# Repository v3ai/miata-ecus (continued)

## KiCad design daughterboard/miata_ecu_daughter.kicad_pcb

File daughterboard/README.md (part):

# Miata ECU — daughterboard rev 0.10 (routed, unverified)

125 × 76 mm, **6 layers**. All SMD parts are on top; the two 1×40 2.54 mm male headers are mounted on the
**bottom side** (plastic under the board, pins pointing down) so the board plugs straight into female
headers on the year-specific motherboard. J1 on the top edge carries power and outputs, J2 on the
bottom edge carries inputs, comms and the LSU 4.9 wideband sensor.

## What changed in rev 0.10
Same outline, same J1/J2 pinout except J2-24 / J2-25; **six layers** instead of four. A rev 0.10 daughterboard goes
with motherboard rev 0.13 (1989-95) or 0.9 (1996-2005); it also fits the earlier motherboards, without the new
inputs. Background and numbers: `VERIFICATION.md`, [Rev 0.10](../VERIFICATION.md#rev-010-six-layers-injector-clamps-card-socket-two-more-inputs-2026-11-13),
and the audit in `research/rev0.10_design_audit.md`.
- **Injector clamp per injector** (D42-D45 ES1D, D46-D49 TPSMC16A): a fast diode from each injector driver's drain to
  a 16 V TVS that returns to the battery input. The turn-off energy goes there instead of through the driver's own
  clamp: 8.8 mJ per shot instead of 15.3 mJ with 20 mH injectors, peak 32 V instead of 43 V. The injector current
  takes about 0.16 ms longer to fall, so **check the injector dead time in the tune**.
- **220 Ω in series with each low-side driver input** (R152-R159): ST's VND7NV04 rating asks for at least 150 Ω.
- **microSD socket** J4 (Molex 47219-2001, hinged lid) on SPI2 with 47 kΩ pull-ups on every line but the clock.
  Rated -20 to +85 °C.
- **Two more inputs on J2-24 and J2-25** (a spare UART up to rev 0.9): flex-fuel sensor frequency (PC6, 10 µs filter)
  and nitrous arm (PC7, 100 µs filter), each through 10 kΩ and clamped to 3.3 V. The motherboard adds the sensor's
  pull-up and the switch's pull-down.
- **Check-engine lamp** driven from its processor pin directly (R160), outside the shared driver enable, so the
  firmware can light it on a fatal error.
- **Battery voltage** sensed at the battery input itself (was after the reverse diode and fuse, 0.3-0.4 V low).
- **Logic supply:** fuse F1 1.1 A hold (was 0.5 A), inductor L1 2.2 µH 7 A moulded, 100 nF (C71) at the buck
  converter's input pins.
- **Six layers:** F.Cu, ground plane, two inner signal layers, +3V3 plane, B.Cu. Every rev 0.9 part keeps its place
  except U14, F1, L1, the LED column (1.5 mm lower), the debug pads J3 and the two input clamps D36/D37 with their
  resistors. Inner copper is 15 µm against 35 µm outside, so the injector, valve, logic-supply and USB-supply nets
  stay on the outer layers; `scripts/track_current.py` checks every current-carrying track against its layer.
- **Heat:** each clamp TVS stands under its driver on its own copper column on all four signal layers (about
  176-196 mm² effective). A model of the whole board (`firmware/tools/board_thermal.py`) puts the board 23-31 °C
  above the air around it at sustained 7200 rpm with 20 mH injectors, the injector drivers 30-41 °C, the clamp TVSs
  43-52 °C and the processor 32-40 °C (sequential; 1989-93 cars run warmer, see `VERIFICATION.md`).
- **Routed from scratch** (`scripts/daughter_make.sh`): `route.py` in six-layer mode, then the new exact-geometry
  finisher `scripts/finish_route.py` for the connections and plane vias the grid router left. DRC: 0 unconnected,
  0 clearance errors.

## What changed in rev 0.9
Layout only; the circuit is rev 0.8's.
- **J1 back on the top edge, J2 on the bottom edge**, as up to rev 0.7, with the four mounting holes in the corners.
  The 16 mm strip of output drivers that rev 0.8 put above J1 now sits just below it: each VND7NV04 (Q1-Q8) stands
  with its tab up against its own J1 pin and its leads facing the level shifters, and the relay switches, the
  ignition diodes and pull-down switches and their resistors are mirrored the same way. Everything else keeps its
  rev 0.8 place and copper.
- **Drain copper** per driver: 84-100 mm² on F.Cu and 95-108 mm² on each of In2.Cu and B.Cu (the column now runs from the board edge down past the driver's leads), joined by 34-42 thermal vias (most in the tab pad; order them filled and
  capped). Estimated junction to ambient 48 °C/W, as in rev 0.8 (sequential injectors at 90 % duty, 7200 rpm, 85 °C ambient: 109 °C).
- **On the motherboards** the daughterboard sits 16 mm lower, centred top to bottom (42 mm from the top edge, as up to
  rev 0.7): JD1 and the upper standoffs are at their rev 0.7 places, JD2, the lower standoffs and the AUX header 16 mm
  lower. A rev 0.9 daughterboard needs a motherboard of rev 0.9 or later (1989-95; 1989-93 is now rev 0.11) or 0.7 (1996-2005).
- **Re-routed incrementally:** the rev 0.8 copper was kept everywhere except the nets of the moved parts
  (`route_eco.py`), which `route.py` routed again; four connections were finished by hand (`hand_route_all.py`).
  DRC: 0 unconnected, 0 clearance errors.

## What changed in rev 0.8
Fixes for what the rev 0.7 checks still flagged (`VERIFICATION.md`, [Rev 0.8](../VERIFICATION.md#rev-08-driver-temperature-and-protected-outputs)):
driver temperature, unprotected relay and ignition outputs, the sensor 5 V, the LSU drive wires, the CAN transceivers
and the AUX UART. Existing designators are unchanged where the part stays; new parts have new numbers.
- **Board 16 mm taller (125 × 76 mm).** The new strip along the top edge, above J1, sits over free motherboard space
  on every year (nothing on any motherboard is under it). J1, J2 and the four holes keep their places relative to each
  other, so the motherboards' sockets and standoffs don't move.
- **Low-side drivers Q1-Q8: ST VND7NV04** (DPAK, C155605) instead of the NCV8406A (SOT-223): 60 mΩ instead of 90-210,
  a 200 mJ clamp rating and 2.1 °C/W junction to case. They stand in the new strip, each with its tab down onto its
  own J1 pin, on a column of drain copper on F.Cu, In2.Cu and B.Cu (about 300 mm² per driver over the three layers)
  joined by 28-34 thermal vias, most of them inside the tab pad (`scripts/tab_copper.py`). Estimated junction to
  ambient 48 °C/W (rev 0.7: 109). Sequential injectors at 90 % duty, 7200 rpm, worst-case Rds(on): 84 °C at 60 °C
  ambient, 110 °C at 85 °C (rev 0.7: thermal shutdown). This is the "heat sink": copper and vias, no bolt-on part,
  since the board sits flat in the stock case. **Order the board with the vias epoxy-filled and capped** (JLC's
  via-in-pad process) so solder doesn't wick away from the tabs.
- **Relay, lamp and tach outputs: seven ZXMS6004FF protected low sides** (Q9-Q15, Diodes IntelliFET: current limit,
  thermal shutdown, 60 V clamp) instead of the ULN2003, driven at 5 V by a second SN74LVC4245A (U12) on the same
  enable as the other drivers, with 10k pull-downs (RN2, RN3). A relay or lamp wire shorted to battery now limits
  instead of burning a ULN channel.
- **Ignition outputs protected:** each TC4427 channel sources through its 100 Ω (now 1206) and a B5819W Schottky
  (D31-D34), and a ZXMS6004FF (Q16-Q19, gates from a 74HCT04, U13) pulls the output low. A coil wire shorted to battery
  just reverse-biases the Schottky. R144-R147 (3.3k, 1206) give the spark edge a defined fall with the pull-down off;
  3.3k keeps them inside their rating with a coil wire held at 24 V.
- **Protected harness 5 V:** a second TLS115 (U14) tracking +5V, out on J1 pin 13 (was a ground pin) to the harness's
  sensor 5 V cavities and the AUX header. The first TLS115 now feeds only the MAP sensor on the motherboard, so a
  sensor 5 V wire shorted to battery no longer takes the MAP reading or back-feeds the board. CLT/IAT bias from it;
  the hall pull-ups from it through a common-anode Schottky pair (D35), so a crank or cam wire shorted to battery
  puts nothing into its pull-up.
- **+3V3 shunt clamp:** a TL431 (U15) at 3.56 V drives a BCP53 PNP (Q20) that sinks fault current pushed into +3V3
  through the input clamps, with 2 × 100 µF bulk (C63, C68). Simulated with 1 A pushed in: 3.93 V peak for the first
  microseconds, then 3.56 V (the MCUs' absolute maximum is 4.0 V).
- **LSU drive wires:** F2 (0.1 A PTC) in the VM wire, Schottky clamps from the pump (D40) and virtual-ground (D41)
  drive nodes to +3V3, R108-R110 in 1206 and R137 22k. A short of IP, RT or VM to battery no longer reaches U101's
  outputs or the F103; the 1206 resistors take the short while it lasts (check or replace them after one).
  Firmware: VM_RESISTOR_VALUE 11.6 Ω (R109 + F2).
- **CAN: TI TCAN1042V-Q1** (U10, U106) instead of the SN65HVD230: ±58 V bus fault protection and −40 to 125 °C.
  Supplied from +5V (C67, C122), with 3.3 V I/O.
- **AUX UART:** 10k series resistors (R139, R140) and BAT54S clamps (D36, D37) on PC6/PC7.
- **Battery and ignition sense:** BAT54WS clamps D38/D39 on the dividers' ADC nodes.
- **Switch inputs: 22k/10k dividers** (was 33k): a 12 V signal at 9 V cranking now gives 2.81 V at the MCU, above ST's
  tested 2.31 V threshold. The hall series resistors R61/R63 are 0603.
- **Status LEDs:** comms and warning moved from PD13/PD14 to PC8/PC9 (PD12 run and PD15 error unchanged); the four
  adjacent PD pins left no way out for the fourth LED line. The board firmware is updated to match.
- **Re-routed incrementally** from the rev 0.7 copper (the old layout moved down 16 mm, `scripts/route_eco.py`), then
  `route.py`'s finish passes. The last connections around the wideband MCU and the LED lines were routed by hand
  (`scripts/hand_route.py`, chained by `hand_route_all.py`; a few short nets ripped up and rerouted in a better order),
  and `scripts/clean_dangling.py` removed the stubs that left. DRC: 0 unconnected, 0 clearance errors.

## What changed in rev 0.7
Fixes for the findings of the 2026-11-02 expanded circuit simulation and fault checks (`VERIFICATION.md`, findings
N1-N9). Existing designators are unchanged; new parts have new numbers.
- **U4 is an ST LDL1117S33R** (low dropout, same SOT-223 pinout) instead of the AMS1117-3.3. With about 1 V of dropout,
  the AMS1117 let the wideband MCU's VDDA (REF3033) run up to 0.95 V above its VDD while +5V rose or fell (power-up,
  key-off, crank dips; ST allows 0.3 V). The new part also keeps +3V3 up through an ISO 16750-2 level II crank, and
  is rated from -40 C.
- **D30 (BAT54WS) from the wideband MCU's VDDA to +3V3.** The low-dropout regulator alone still let VDDA lead VDD by
  about 0.8 V at key-off and in a slow brown-out, when the REF3033 holds up longer than +3V3; the Schottky caps the
  difference at about 0.25 V in every case simulated.
- **Clamps on the eight analog inputs:** D19-D26 (BAT54WS Schottky) from each AN_ node to +3V3, after the 5.6k. A
  sensor wire shorted to battery put 9.2 V on its MCU pin; now about 3.55 V, with 1.9 mA into +3V3 instead of the
  MCU. The 5.6k series and the CLT/IAT 2.7k bias resistors are now 0603. A Schottky leaks a little into the input
  when the sensor reads near 0 V, more when hot: estimated 5 mV at the sensor at 60 °C (up to about 46 mV with a
  worst-case part). Compare TPS and CLT readings with a meter on a hot day.
- **Clamps on the three 12 V switch inputs:** D27-D29 (1N4148WS) to +3V3, as on the hall inputs (a battery-fed switch
  closed during a load dump overdrove the pin). D27/D28 stand between the series resistors; D29 lies below the VR2
  parts.
- **Hall input resistors in 0603:** a crank/cam wire shorted to 14.4 V puts 88 mW into its 1k pull-up. The pull-ups
  now stand vertically beside their 4.7k series resistors to fit the larger size.
- **Knock input:** R138 (2.2k) ahead of the coupling cap C44, so a knock wire shorted to battery no longer couples a
  14 V step straight into the op-amp's input diodes.
- **Wideband sense inputs:** R137 (10k) feeds the Nernst buffer (U101 pin 10) from the LSU_UN wire, and F103 PA1 is no
  longer wired to LSU_VM (the firmware never sampled it). A UN or VM wire shorted to battery no longer reaches those
  inputs directly. The pump and virtual-ground drive paths can't take series resistance, so a short of IP, RT or VM
  to battery still damages U101 (inherited from the FOME module).
- **Injector driver copper:** OUT_INJ1-4 copper zones on both outer layers around Q1-Q4's tabs (86-90 mm² each), with
  17-21 thermal vias each. Estimated junction-to-ambient 109 °C/W instead of 130. This helps but doesn't remove the
  limit: at sustained 90 % injector duty a driver still reaches thermal shutdown at 85 °C ambient (1989-93), and on
  the sequential years, where each driver also absorbs its injector's turn-off energy, already at 60 °C near 7200 rpm.
  See VERIFICATION.md, N8.
- **Re-routed incrementally:** only the nets around the changed parts were routed again; the rest of the rev 0.6
  copper is unchanged. DRC: 0 unconnected, 0 clearance.

## What changed in rev 0.6
- **Wideband MCU: STM32F103C8T6** (U102, LQFP-48) instead of the STM32F042K6T6, which has been scarce for years and
  was down to about 100 at JLCPCB/LCSC; the F103C8T6 has over 200k there. The module's analog front end is unchanged.
  - Pins: ESR drives and LEDs face left, heater PWM / battery sense / pump PWM / BOOT1 right, CAN and the
    programming UART up, analog inputs down (`scripts/wideband.py`, U2_PADS).
  - New parts: an 8 MHz crystal Y101 with 33 pF loads C119/C120 (the same crystal as the main MCU's; keeps CAN
    timing in spec over temperature), R135 holds BOOT1 low, C121 decouples the third VDD pin.
  - Programming link unchanged: PD8/PD9 to the F103's USART1 (PA10/PA9), PD10 to BOOT0, PD11 to NRST.
  - Firmware: rusEFI's wideband controller with this board's port (`firmware/wideband/miata_f1`), carried by the
    main firmware and written with "Flash on-board wideband". rusEFI's own over-CAN wideband update is for the F042
    module and does not apply.

## What changed in rev 0.5
The fixes from the verification review (`VERIFICATION.md` in the repository root). Existing designators are unchanged;
new parts have new numbers.
- **Parts JLCPCB stocks (rev 0.5b).** JLCPCB's BOM check found ten lines short of stock. The replacements fit the
  same footprints; details in `VERIFICATION.md`.
  - Q1-Q8: onsemi **NCV8406A** (SOT-223, same pinout, 60-70 V active clamp, current limit and thermal shutdown)
    instead of the AUIPS2041L.
  - F1: TECHFUSE nSMD050-33V (33 V rating). D11/D12: Littelfuse SMAJ33A. L1: FH CMI322513U2R2KT.
    Status LEDs: Hubei KENTO KT-0603 G/B/Y. C103: YAGEO 33 nF 50 V. R110: 62 Ω (was 61.9 Ω, inside its 1 % tolerance).
  - VR inputs (spares, no Miata year uses a VR sensor): U9 is now a **LM2903** dual comparator (TI, onsemi, UMW and
    others make it) instead of the MAX9926, which is out of stock everywhere. Each input gets a BAT54S clamp to GND
    and +5V and 100k to a 1.65 V bias, and each output 1M of hysteresis (D15-D18, R73-R80, C60). The board was
    re-routed for these parts; `scripts/daughter_patch.py` adds the one track the autorouter left open (HALL1,
    through a via under the MCU) and nudges AN_AUX3 clear of the new clamps.
  - `fab/jlcpcb_cpl.csv` now uses the gerbers' own coordinates (no offset), with JLC's rotation corrections for
    SOT-223, TO-252, SOT-23, SOIC, TSSOP, LQFP and the resistor arrays, read off JLC's placement preview.
  - From the parts-availability review: D6 is now Littelfuse's SMCJ30A and D9 a Diodes B360A (both mainstream
    parts stocked at JLCPCB and US distributors; same footprints and ratings).
  - U105's footprint is named SOT-23-5 to match the AD8628ARTZ (identical pads), and SW1/SW2 share one BOM line.
- **5 V drive for the low-side drivers.** The rev 0.4 drivers (AUIPS2041) are specified at a 4-5.5 V input, and
  rev 0.4 drove them at 3.3 V.
  - U11 (SN74LVC4245A, DIR low: B → A) now drives Q1-Q8 from the MCU's control pins.
  - Its output enable is pulled up (R71), so the injectors, idle valve, VVT, boost and alternator stay off through
    reset, boot, the bootloader and DFU. The firmware enables them on **PA8** (open drain, active low) once every
    output is configured. This also covers PB3/PB4's power-up states (SWO trace, JTAG pull-up).
  - R19-R26 now pull the driver side low. The firmware parks unused control pins with the MCU's pull-downs
    (rusEFI's own idea of an unused pin is a pull-up, which would turn the driver on).
- **BOOT1 (PB2) pulled low** (R72), so ST's USB DFU bootloader starts reliably.
- **No relay back-feed.** The ULN2003's COM pin goes to an SMAJ33A TVS (D11, 36.7-40.6 V breakdown) instead of
  +12V. A battery-fed relay coil (the 2003-05 main relay) can no longer power the ECU through the clamp diodes with
  the key off. Relay kick-back clamps at 43 V at most (ULN2003 limit 50 V), and the TVS stays off through a 35 V load
  dump on the relay feeds.
- **Fused, clamped logic supply.** D7 (battery) and D8 (ignition wake) feed F1 (0.5 A PTC), then D12 (SMAJ33A) on +12V.
  - This keeps the buck under its 44 V maximum in load-dump and ISO pulse tests, and clamps the ignition path too.
    D12's breakdown sits above the 35 V load-dump clamp, so the input TVS D6 takes that energy and D12 only sees fast
    spikes.
  - An internal short trips F1 instead of waiting on the car's fuse.
  - C16 is now 10 µF / 50 V, D9 is a 60 V 3 A Schottky (Diodes B360A), and C59 adds buck output capacitance.
- **Crank/cam input clamps.** D13/D14 (1N4148WS) clamp PE7/PE8 to +3V3. These 5 V-tolerant pins have no clamp of
  their own, so a crank/cam wire shorted to battery would otherwise destroy them.
- **Buck inductor L2** is now a Sunlord MWSA0603S-100MT (7 × 6.6 mm, 5.5 A saturation), above the LMR14020's
  3.8 A maximum current limit. The old 5 × 5 mm part saturated at 3.5 A.
- **Crystal load caps** C13/C14 are 33 pF (were 22 pF) to match the 20 pF crystal.
- The Tag-Connect SWD pads J3 moved right of the MCU to make room for U11.

## What changed in rev 0.4
- **Both MCUs flash over the one USB-C port.** The main MCU now has a programming link to the wideband MCU (U102):
  | Main MCU (U1, STM32F407) | Wideband MCU (U102, STM32F042) | Job |
  |---|---|---|
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
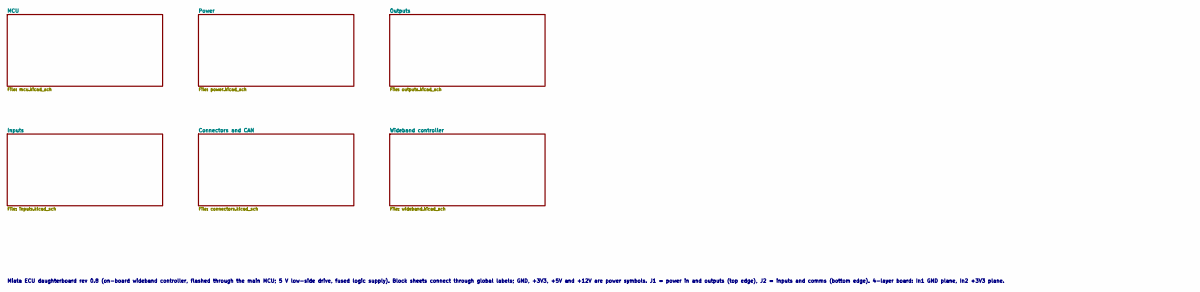
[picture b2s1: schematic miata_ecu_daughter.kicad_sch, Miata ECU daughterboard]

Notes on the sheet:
Miata ECU daughterboard rev 0.8 (on-board wideband controller, flashed through the main MCU; 5 V low-side drive, fused logic supply). Block sheets connect through global labels; GND, +3V3, +5V and +12V are power symbols. J1 = power in and outputs (top edge), J2 = inputs and comms (bottom edge). 4-l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

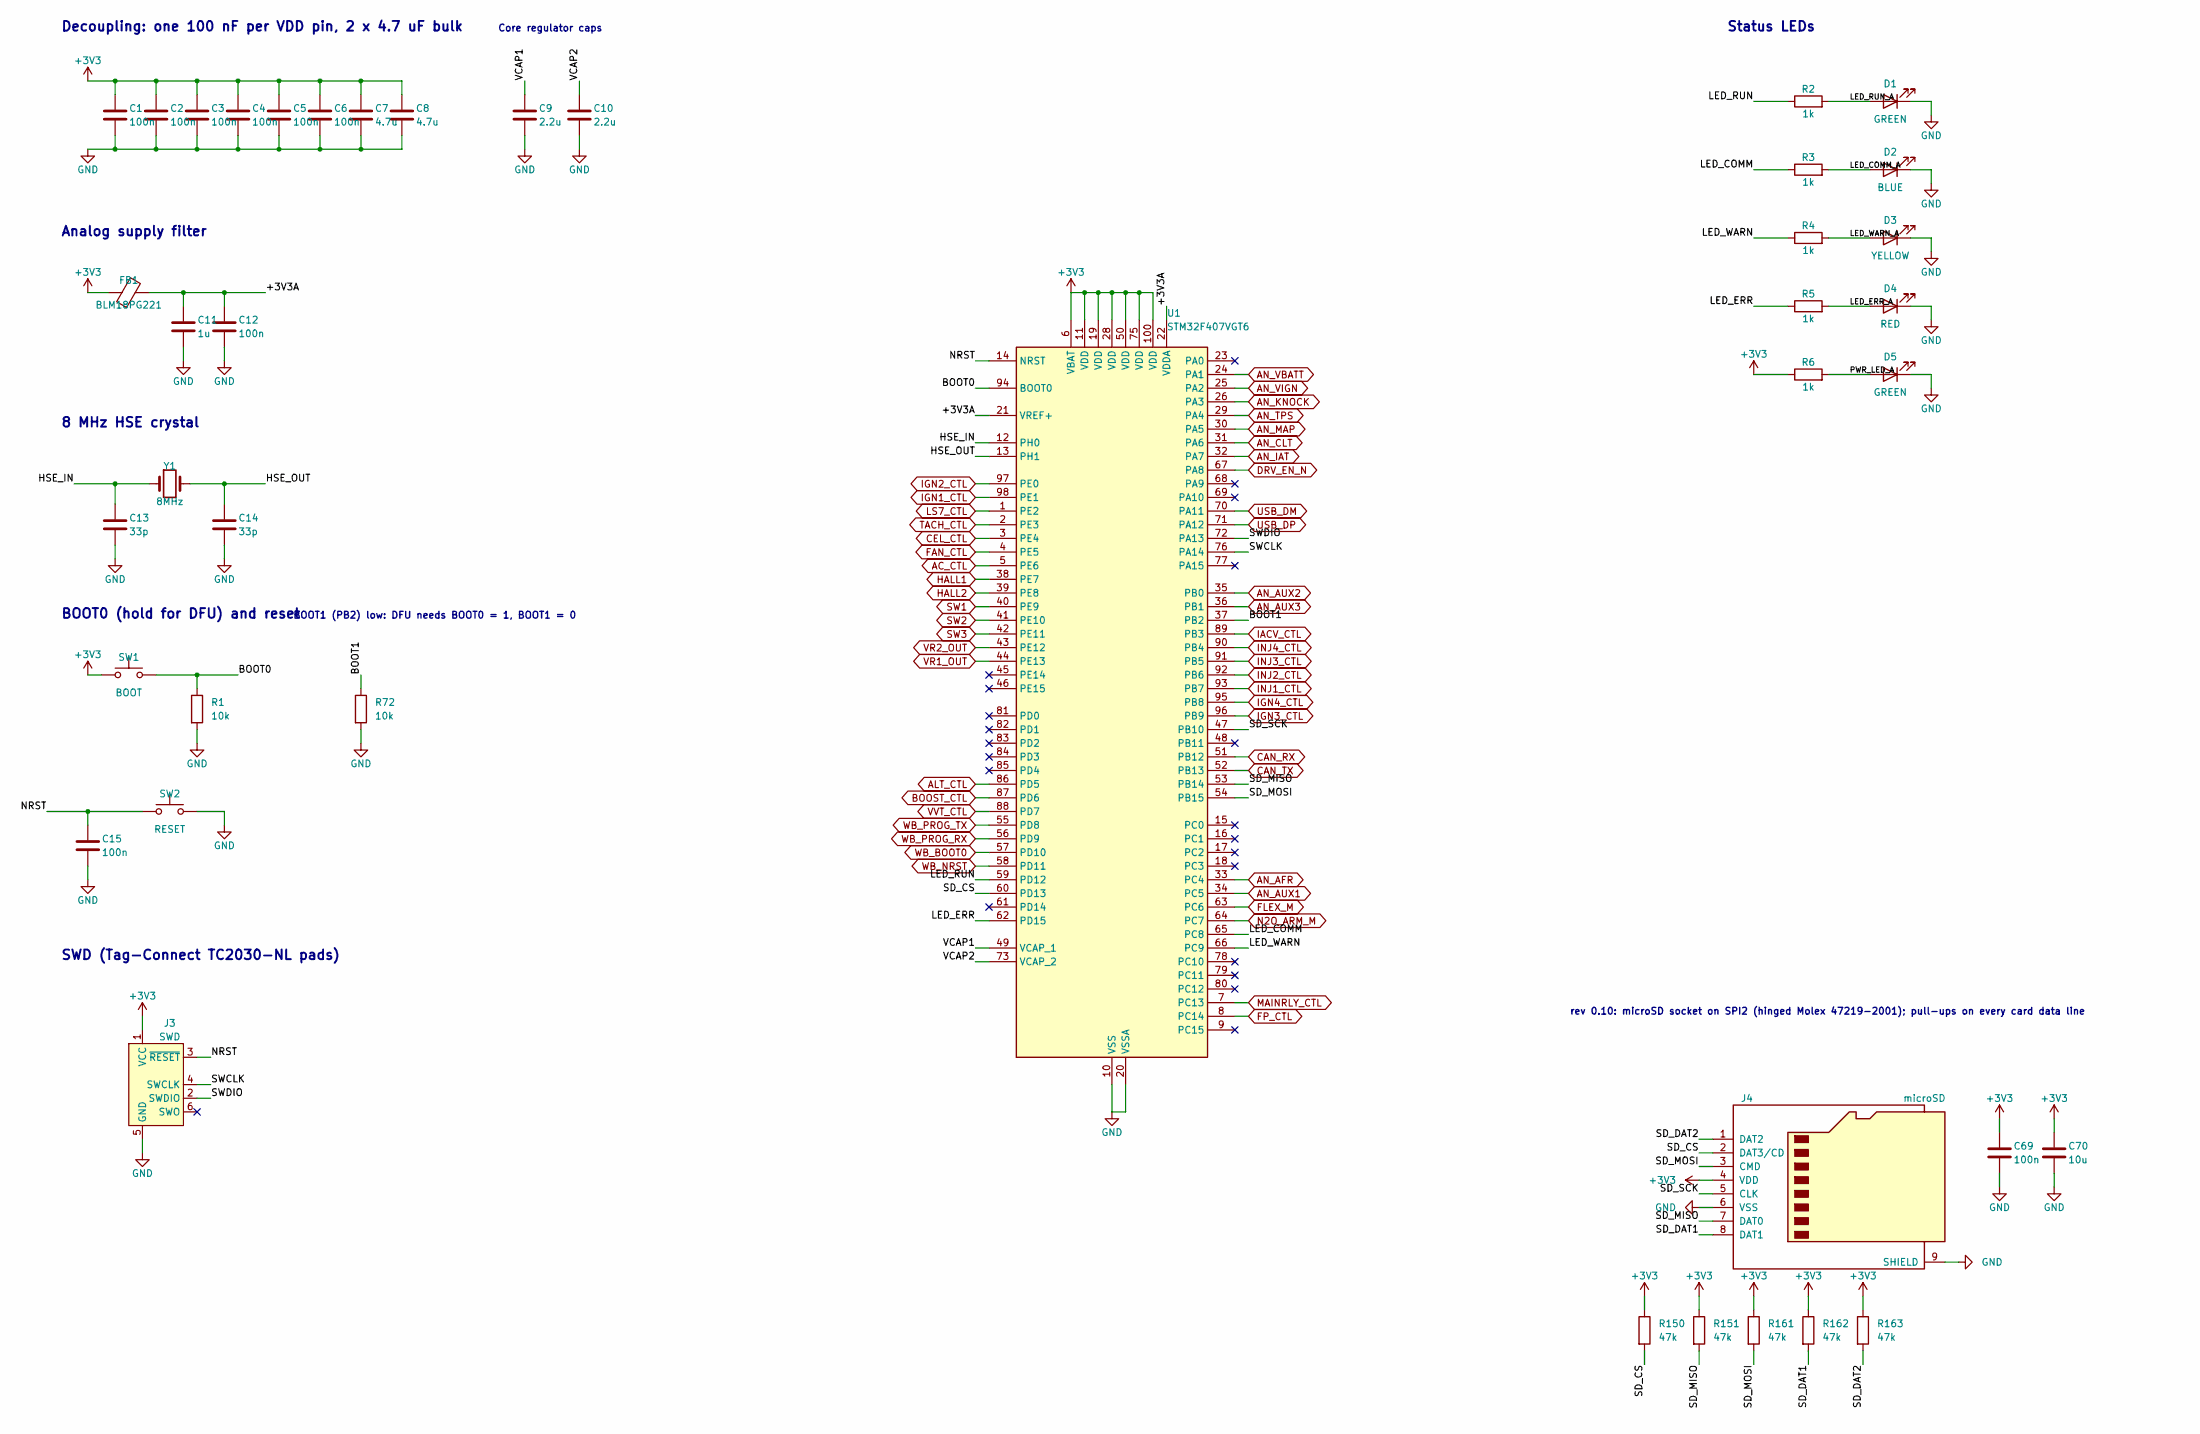
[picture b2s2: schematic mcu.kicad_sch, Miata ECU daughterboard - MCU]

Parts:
C1, C2, C3, C5, C6, C12, C15: 100n; C_0603_1608Metric; LCSC C14663
C4, C69: 100n; C_0402_1005Metric; LCSC C1525
C7, C8: 4.7u; C_0603_1608Metric; LCSC C19666
C9, C10: 2.2u; C_0603_1608Metric; LCSC C23630
C11: 1u; C_0603_1608Metric; LCSC C15849
C13, C14: 33p; C_0603_1608Metric; LCSC C1663
C70: 10u; C_0805_2012Metric; LCSC C15850
D1, D5: GREEN; LED_0603_1608Metric; LCSC C12624
D2: BLUE; LED_0603_1608Metric; LCSC C2288
D3: YELLOW; LED_0603_1608Metric; LCSC C2287
D4: RED; LED_0603_1608Metric; LCSC C2286
FB1: BLM18PG221; L_0603_1608Metric; LCSC C80165
J3: SWD; Tag-Connect_TC2030-IDC-NL_2x03_P1.27mm_Vertical
J4: microSD; microSD_HC_Molex_47219-2001; LCSC C164170
R1: 10k; R_0603_1608Metric; LCSC C25804
R2, R3, R4, R5, R6: 1k; R_0603_1608Metric; LCSC C21190
R72: 10k; R_0402_1005Metric; LCSC C25744
R150, R151, R161, R162, R163: 47k; R_0402_1005Metric; LCSC C25792
SW1: BOOT; SW_Push_1P1T_XKB_TS-1187A; LCSC C318884
SW2: RESET; SW_Push_1P1T_XKB_TS-1187A; LCSC C318884
U1: STM32F407VGT6; LQFP-100_14x14mm_P0.5mm; LCSC C12345
Y1: 8MHz; Crystal_SMD_5032-2Pin_5.0x3.2mm; LCSC C115962

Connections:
+3V3: C1.1, C2.1, C3.1, C4.1, C5.1, C6.1, C7.1, C8.1, C69.1, C70.1, FB1.1, J3.1 (VCC), J4.4 (VDD), R6.1, R150.1, R151.1, R161.1, R162.1, R163.1, SW1.1, U1.6 (VBAT), U1.11 (VDD), U1.19 (VDD), U1.28 (VDD), U1.50 (VDD), U1.75 (VDD), U1.100 (VDD); also elsewhere on the board
/MCU/+3V3A: C11.1, C12.1, FB1.2, U1.21 (VREF+), U1.22 (VDDA)
/MCU/BOOT0: R1.1, SW1.2, U1.94 (BOOT0)
/MCU/BOOT1: R72.1, U1.37 (PB2)
/MCU/HSE_IN: C13.1, U1.12 (PH0), Y1.1
/MCU/HSE_OUT: C14.1, U1.13 (PH1), Y1.2
/MCU/LED_COMM: R3.1, U1.65 (PC8)
/MCU/LED_COMM_A: D2.2 (A), R3.2
/MCU/LED_ERR: R5.1, U1.62 (PD15)
/MCU/LED_ERR_A: D4.2 (A), R5.2
/MCU/LED_RUN: R2.1, U1.59 (PD12)
/MCU/LED_RUN_A: D1.2 (A), R2.2
/MCU/LED_WARN: R4.1, U1.66 (PC9)
/MCU/LED_WARN_A: D3.2 (A), R4.2
/MCU/NRST: C15.1, J3.3 (~RESET), SW2.1, U1.14 (NRST)
/MCU/PWR_LED_A: D5.2 (A), R6.2
/MCU/SD_CS: J4.2 (DAT3/CD), R150.2, U1.60 (PD13)
/MCU/SD_DAT1: J4.8 (DAT1), R162.2
/MCU/SD_DAT2: J4.1 (DAT2), R163.2
/MCU/SD_MISO: J4.7 (DAT0), R151.2, U1.53 (PB14)
/MCU/SD_MOSI: J4.3 (CMD), R161.2, U1.54 (PB15)
/MCU/SD_SCK: J4.5 (CLK), U1.47 (PB10)
/MCU/SWCLK: J3.4 (SWCLK), U1.76 (PA14)
/MCU/SWDIO: J3.2 (SWDIO), U1.72 (PA13)
/MCU/VCAP1: C9.1, U1.49 (VCAP_1)
/MCU/VCAP2: C10.1, U1.73 (VCAP_2)
AC_CTL: U1.5 (PE6); also elsewhere on the board
ALT_CTL: U1.86 (PD5); also elsewhere on the board
AN_AFR: U1.33 (PC4); also elsewhere on the board
AN_AUX1: U1.34 (PC5); also elsewhere on the board
AN_AUX2: U1.35 (PB0); also elsewhere on the board
AN_AUX3: U1.36 (PB1); also elsewhere on the board
AN_CLT: U1.31 (PA6); also elsewhere on the board
AN_IAT: U1.32 (PA7); also elsewhere on the board
AN_KNOCK: U1.26 (PA3); also elsewhere on the board
AN_MAP: U1.30 (PA5); also elsewhere on the board
AN_TPS: U1.29 (PA4); also elsewhere on the board
AN_VBATT: U1.24 (PA1); also elsewhere on the board
AN_VIGN: U1.25 (PA2); also elsewhere on the board
BOOST_CTL: U1.87 (PD6); also elsewhere on the board
CAN_RX: U1.51 (PB12); also elsewhere on the board
CAN_TX: U1.52 (PB13); also elsewhere on the board
CEL_CTL: U1.3 (PE4); also elsewhere on the board
DRV_EN_N: U1.67 (PA8); also elsewhere on the board
FAN_CTL: U1.4 (PE5); also elsewhere on the board
FLEX_M: U1.63 (PC6); also elsewhere on the board
FP_CTL: U1.8 (PC14); also elsewhere on the board
GND: C1.2, C2.2, C3.2, C4.2, C5.2, C6.2, C7.2, C8.2, C9.2, C10.2, C11.2, C12.2, C13.2, C14.2, C15.2, C69.2, C70.2, D1.1 (K), D2.1 (K), D3.1 (K), D4.1 (K), D5.1 (K), J3.5 (GND), J4.6 (VSS), J4.9 (SHIELD), R1.2, R72.2, SW2.2, U1.10 (VSS), U1.20 (VSSA), U1.27 (VSS), U1.74 (VSS), U1.99 (VSS); also elsewhere on the board
HALL1: U1.38 (PE7); also elsewhere on the board
HALL2: U1.39 (PE8); also elsewhere on the board
IACV_CTL: U1.89 (PB3); also elsewhere on the board
IGN1_CTL: U1.98 (PE1); also elsewhere on the board
IGN2_CTL: U1.97 (PE0); also elsewhere on the board
IGN3_CTL: U1.96 (PB9); also elsewhere on the board
IGN4_CTL: U1.95 (PB8); also elsewhere on the board
INJ1_CTL: U1.93 (PB7); also elsewhere on the board
INJ2_CTL: U1.92 (PB6); also elsewhere on the board
INJ3_CTL: U1.91 (PB5); also elsewhere on the board
INJ4_CTL: U1.90 (PB4); also elsewhere on the board
LS7_CTL: U1.1 (PE2); also elsewhere on the board
MAINRLY_CTL: U1.7 (PC13); also elsewhere on the board
N2O_ARM_M: U1.64 (PC7); also elsewhere on the board
SW1: U1.40 (PE9); also elsewhere on the board
SW2: U1.41 (PE10); also elsewhere on the board
SW3: U1.42 (PE11); also elsewhere on the board
TACH_CTL: U1.2 (PE3); also elsewhere on the board
USB_DM: U1.70 (PA11); also elsewhere on the board
USB_DP: U1.71 (PA12); also elsewhere on the board
VR1_OUT: U1.44 (PE13); also elsewhere on the board
VR2_OUT: U1.43 (PE12); also elsewhere on the board
VVT_CTL: U1.88 (PD7); also elsewhere on the board
WB_BOOT0: U1.57 (PD10); also elsewhere on the board
WB_NRST: U1.58 (PD11); also elsewhere on the board
WB_PROG_RX: U1.56 (PD9); also elsewhere on the board
WB_PROG_TX: U1.55 (PD8); also elsewhere on the board

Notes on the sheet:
Decoupling: one 100 nF per VDD pin, 2 x 4.7 uF bulk
Core regulator caps
Analog supply filter
8 MHz HSE crystal
BOOT0 (hold for DFU) and reset
BOOT1 (PB2) low: DFU needs BOOT0 = 1, BOOT1 = 0
SWD (Tag-Connect TC2030-NL pads)
rev 0.10: microSD socket on SPI2 (hinged Molex 47219-2001); pull-ups on every card data line
Status LEDs

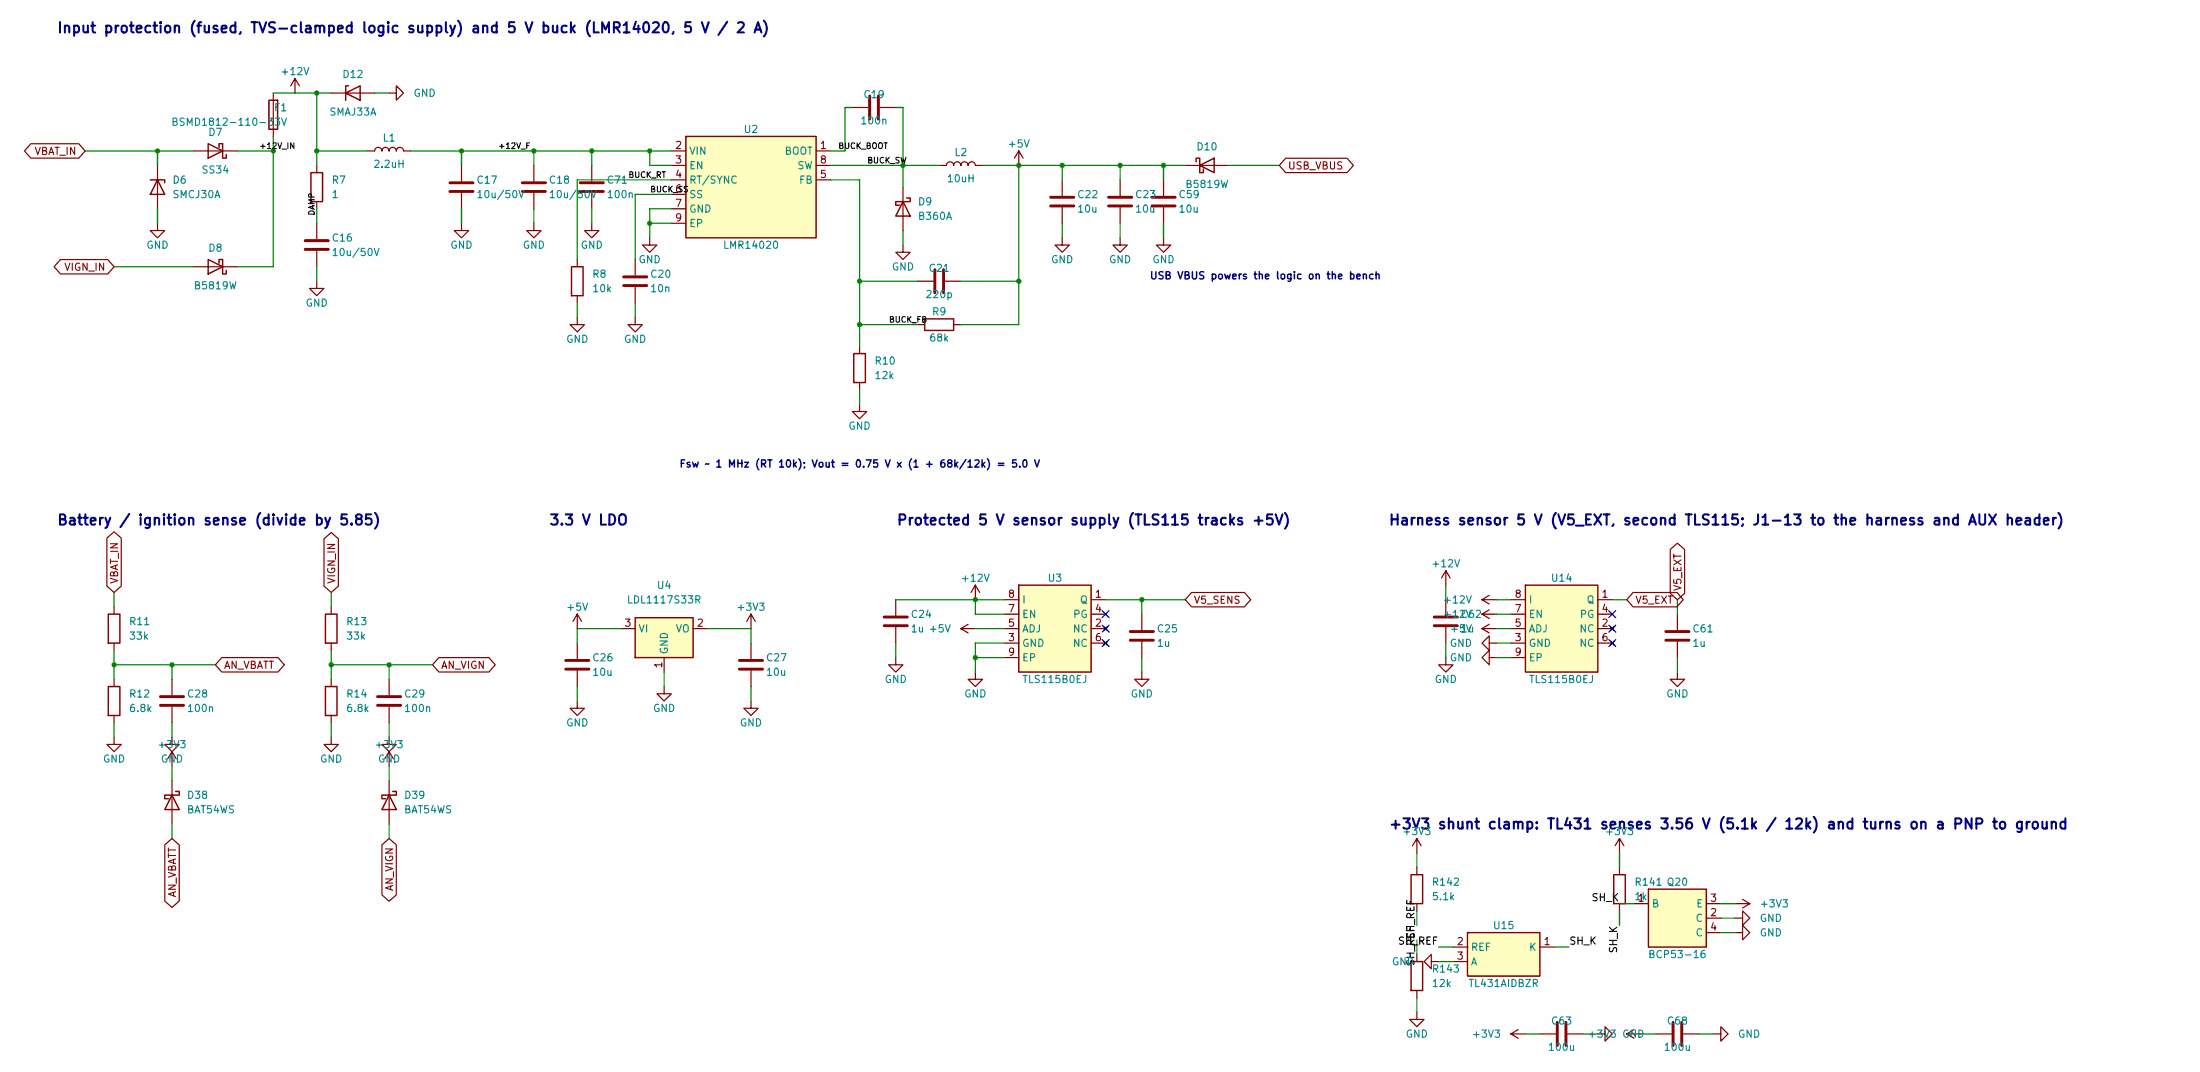
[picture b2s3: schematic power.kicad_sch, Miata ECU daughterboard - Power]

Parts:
C16, C17, C18: 10u/50V; C_1206_3216Metric; LCSC C13585
C19, C71: 100n; C_0603_1608Metric; LCSC C14663
C20: 10n; C_0603_1608Metric; LCSC C57112
C21: 220p; C_0603_1608Metric; LCSC C1603
C22, C23, C26, C27, C59: 10u; C_0805_2012Metric; LCSC C15850
C24, C25, C61, C62: 1u; C_0603_1608Metric; LCSC C15849
C28, C29: 100n; C_0402_1005Metric; LCSC C1525
C63, C68: 100u; C_1206_3216Metric; LCSC C15008
D6: SMCJ30A; D_SMC; LCSC C224048
D7: SS34; D_SMA; LCSC C8678
D8, D10: B5819W; D_SOD-123; LCSC C8598
D9: B360A; D_SMA; LCSC C94193
D12: SMAJ33A; D_SMA; LCSC C223988
D38, D39: BAT54WS; D_SOD-323; LCSC C124205
F1: BSMD1812-110-33V; Fuse_1812_4532Metric; LCSC C883150
L1: 2.2uH; L_Sunlord_MWSA0503S; LCSC C177247
L2: 10uH; L_Sunlord_MWSA0603S; LCSC C132141
Q20: BCP53-16; SOT-223; LCSC C85085
R7: 1; R_0603_1608Metric; LCSC C22936
R8: 10k; R_0603_1608Metric; LCSC C25804
R9: 68k; R_0603_1608Metric; LCSC C23231
R10, R143: 12k; R_0603_1608Metric; LCSC C22790
R11, R13: 33k; R_0402_1005Metric; LCSC C25779
R12, R14: 6.8k; R_0402_1005Metric; LCSC C25917
R141: 1k; R_0603_1608Metric; LCSC C21190
R142: 5.1k; R_0603_1608Metric; LCSC C23186
U2: LMR14020; SOIC-8-1EP_3.9x4.9mm_P1.27mm_EP2.29x3mm; LCSC C187824
U3, U14: TLS115B0EJ; Infineon_PG-DSO-8-27_3.9x4.9mm_EP2.65x3mm; LCSC C3743696
U4: LDL1117S33R; SOT-223-3_TabPin2; LCSC C435835
U15: TL431AIDBZR; SOT-23; LCSC C23892

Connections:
+3V3: C27.1, C63.1, C68.1, D38.1 (K), D39.1 (K), Q20.3 (E), R141.1, R142.1, U4.2 (VO); also elsewhere on the board
+5V: C21.1, C22.1, C23.1, C26.1, C59.1, D10.1 (K), L2.2, R9.1, U3.5 (ADJ), U4.3 (VI), U14.5 (ADJ); also elsewhere on the board
+12V: C24.1, C62.1, D12.1 (K), F1.2, L1.1, R7.1, U3.7 (EN), U3.8 (I), U14.7 (EN), U14.8 (I)
/Power/+12V_F: C17.1, C18.1, C71.1, L1.2, U2.2 (VIN), U2.3 (EN)
/Power/+12V_IN: D7.1 (K), D8.1 (K), F1.1
/Power/BUCK_BOOT: C19.1, U2.1 (BOOT)
/Power/BUCK_FB: C21.2, R9.2, R10.1, U2.5 (FB)
/Power/BUCK_RT: R8.1, U2.4 (RT/SYNC)
/Power/BUCK_SS: C20.1, U2.6 (SS)
/Power/BUCK_SW: C19.2, D9.1 (K), L2.1, U2.8 (SW)
/Power/DAMP: C16.1, R7.2
/Power/SH_K: Q20.1 (B), R141.2, U15.1 (K)
/Power/SH_REF: R142.2, R143.1, U15.2 (REF)
AN_VBATT: C28.1, D38.2 (A), R11.2, R12.1; also elsewhere on the board
AN_VIGN: C29.1, D39.2 (A), R13.2, R14.1; also elsewhere on the board
GND: C16.2, C17.2, C18.2, C20.2, C22.2, C23.2, C24.2, C25.2, C26.2, C27.2, C28.2, C29.2, C59.2, C61.2, C62.2, C63.2, C68.2, C71.2, D6.2 (A), D9.2 (A), D12.2 (A), Q20.2 (C), Q20.4 (C), R8.2, R10.2, R12.2, R14.2, R143.2, U2.7 (GND), U2.9 (EP), U3.3 (GND), U3.9 (EP), U4.1 (GND), U14.3 (GND), U14.9 (EP), U15.3 (A); also elsewhere on the board
USB_VBUS: D10.2 (A); also elsewhere on the board
V5_EXT: C61.1, U14.1 (Q); also elsewhere on the board
V5_SENS: C25.1, U3.1 (Q); also elsewhere on the board
VBAT_IN: D6.1 (K), D7.2 (A), R11.1; also elsewhere on the board
VIGN_IN: D8.2 (A), R13.1; also elsewhere on the board

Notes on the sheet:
Input protection (fused, TVS-clamped logic supply) and 5 V buck (LMR14020, 5 V / 2 A)
USB VBUS powers the logic on the bench
Fsw ~ 1 MHz (RT 10k); Vout = 0.75 V x (1 + 68k/12k) = 5.0 V
3.3 V LDO
Protected 5 V sensor supply (TLS115 tracks +5V)
Harness sensor 5 V (V5_EXT, second TLS115; J1-13 to the harness and AUX header)
+3V3 shunt clamp: TL431 senses 3.56 V (5.1k / 12k) and turns on a PNP to ground
Battery / ignition sense (divide by 5.85)

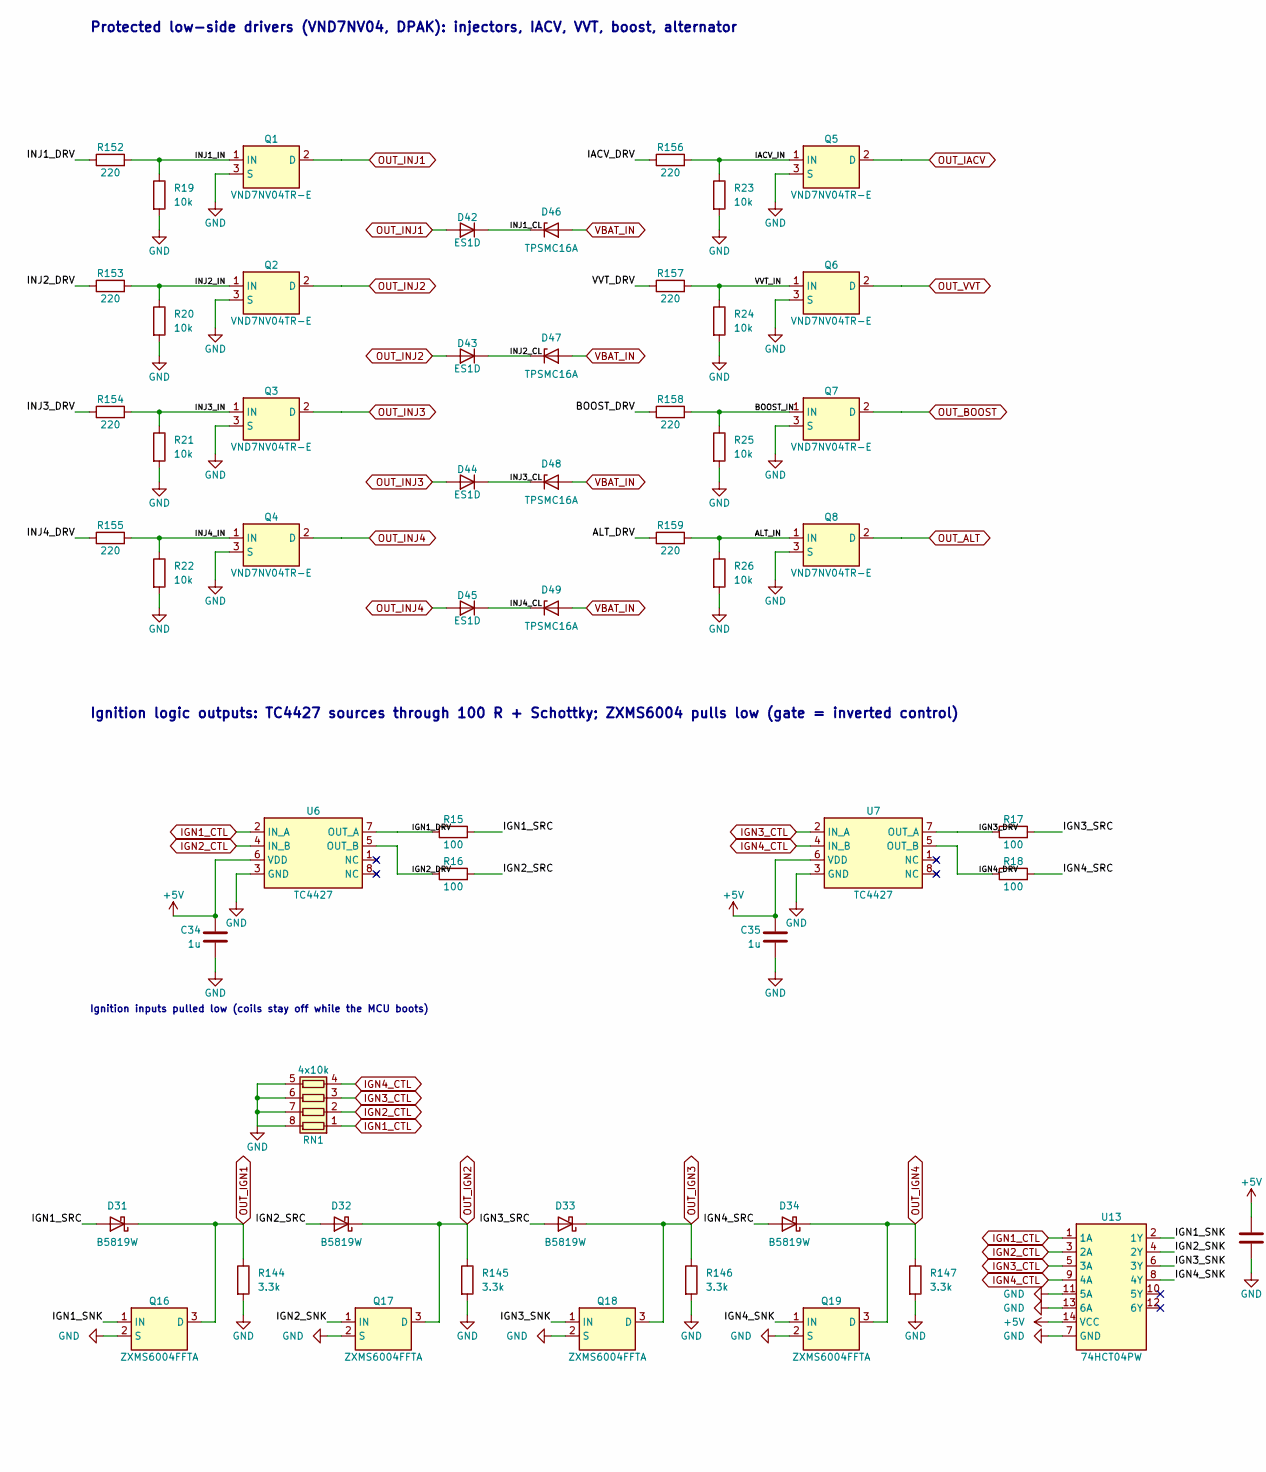
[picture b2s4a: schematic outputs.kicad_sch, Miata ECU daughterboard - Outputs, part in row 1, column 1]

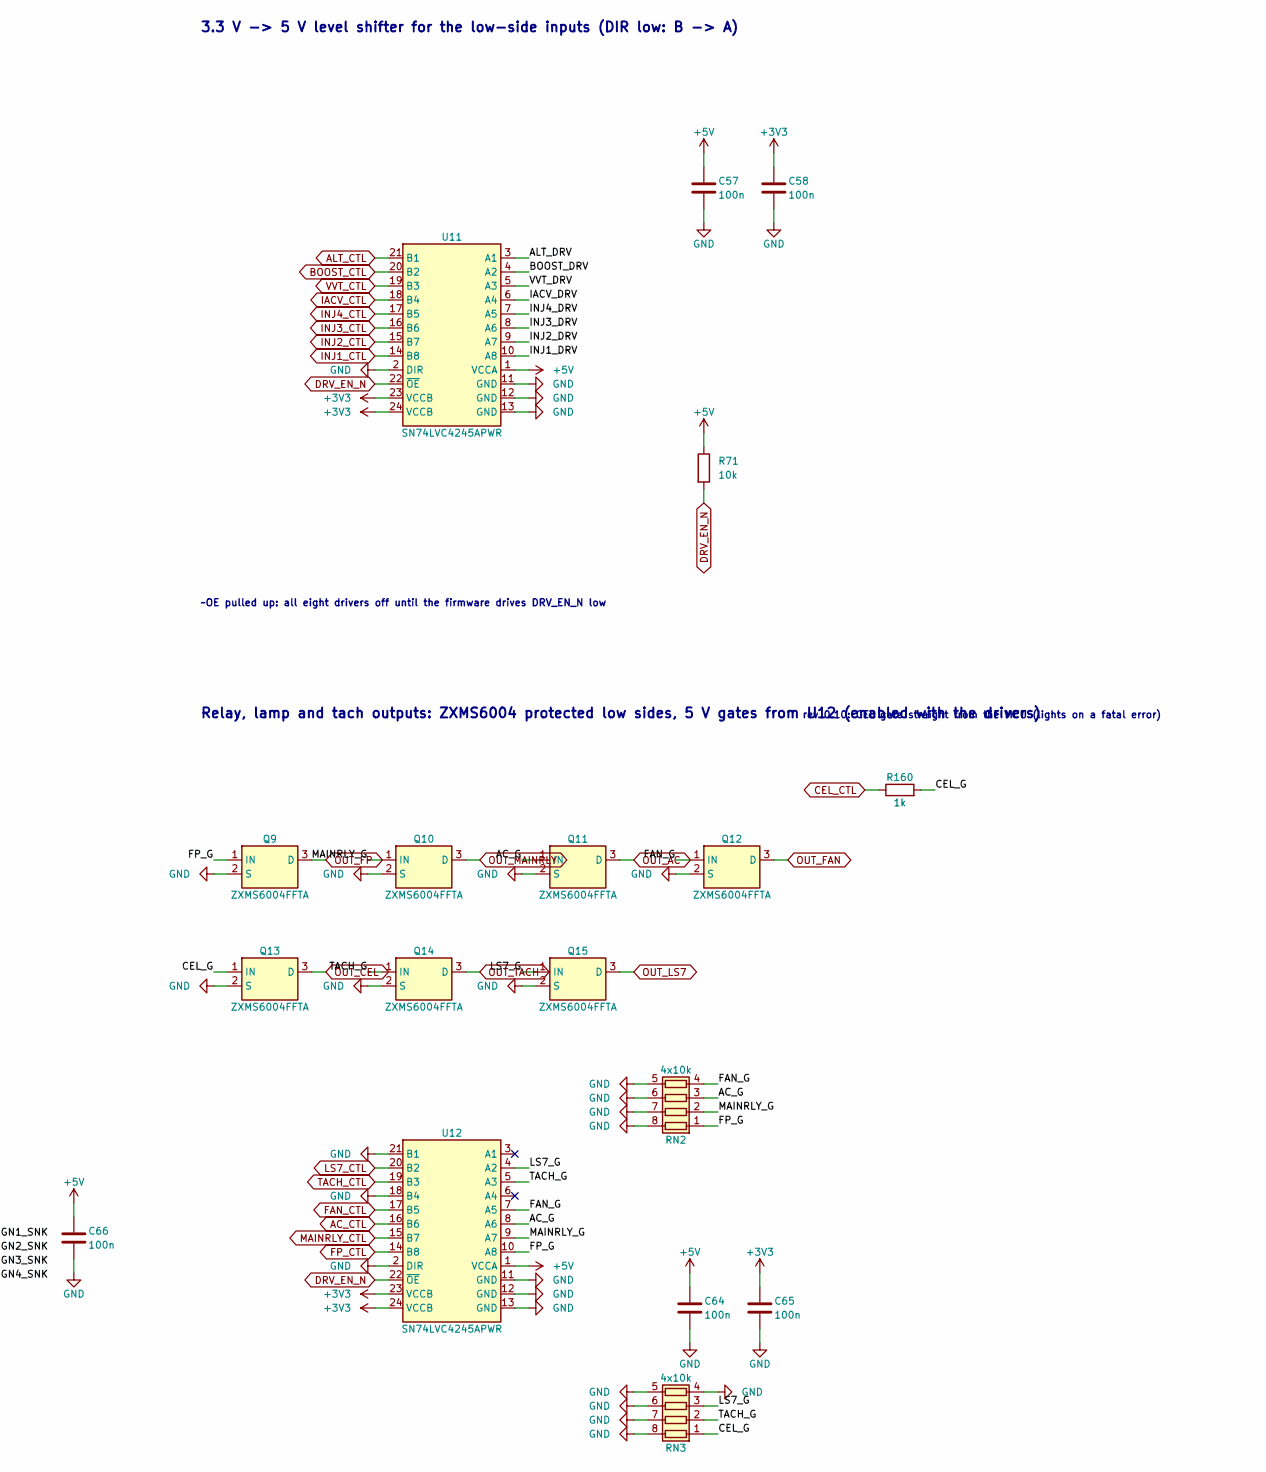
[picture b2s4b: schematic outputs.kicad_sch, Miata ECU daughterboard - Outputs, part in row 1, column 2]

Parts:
C34, C35: 1u; C_0402_1005Metric; LCSC C52923
C57, C58, C64, C65, C66: 100n; C_0402_1005Metric; LCSC C1525
D31, D32, D33, D34: B5819W; D_SOD-123; LCSC C8598
D42, D43, D44, D45: ES1D; D_SMA; LCSC C116492
D46, D47, D48, D49: TPSMC16A; D_SMC; LCSC C1982018
Q1, Q2, Q3, Q4, Q5, Q6, Q7, Q8: VND7NV04TR-E; TO-252-2; LCSC C155605
Q9, Q10, Q11, Q12, Q13, Q14, Q15, Q16, Q17, Q18, Q19: ZXMS6004FFTA; SOT-23; LCSC C95063
R15, R16, R17, R18: 100; R_1206_3216Metric; LCSC C17901
R19, R20, R21, R22, R23, R24, R25, R26: 10k; R_0603_1608Metric; LCSC C25804
R71: 10k; R_0402_1005Metric; LCSC C25744
R144, R145, R146, R147: 3.3k; R_1206_3216Metric; LCSC C26032
R152, R153, R154, R155, R156, R157, R158, R159: 220; R_0402_1005Metric; LCSC C25091
R160: 1k; R_0402_1005Metric; LCSC C11702
RN1, RN2, RN3: 4x10k; R_Array_Convex_4x0603; LCSC C29718
U6, U7: TC4427; SOIC-8_3.9x4.9mm_P1.27mm; LCSC C20551
U11, U12: SN74LVC4245APWR; TSSOP-24_4.4x7.8mm_P0.65mm; LCSC C7859
U13: 74HCT04PW; TSSOP-14_4.4x5mm_P0.65mm; LCSC C131317

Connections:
+3V3: C58.1, C65.1, U11.23 (VCCB), U11.24 (VCCB), U12.23 (VCCB), U12.24 (VCCB); also elsewhere on the board
+5V: C34.1, C35.1, C57.1, C64.1, C66.1, R71.1, U6.6 (VDD), U7.6 (VDD), U11.1 (VCCA), U12.1 (VCCA), U13.14 (VCC); also elsewhere on the board
/Outputs/AC_G: Q11.1 (IN), RN2.3 (R3.1), U12.8 (A6)
/Outputs/ALT_DRV: R159.1, U11.3 (A1)
/Outputs/ALT_IN: Q8.1 (IN), R26.1, R159.2
/Outputs/BOOST_DRV: R158.1, U11.4 (A2)
/Outputs/BOOST_IN: Q7.1 (IN), R25.1, R158.2
/Outputs/CEL_G: Q13.1 (IN), R160.2, RN3.1 (R1.1)
/Outputs/FAN_G: Q12.1 (IN), RN2.4 (R4.1), U12.7 (A5)
/Outputs/FP_G: Q9.1 (IN), RN2.1 (R1.1), U12.10 (A8)
/Outputs/IACV_DRV: R156.1, U11.6 (A4)
/Outputs/IACV_IN: Q5.1 (IN), R23.1, R156.2
/Outputs/IGN1_DRV: R15.1, U6.7 (OUT_A)
/Outputs/IGN1_SNK: Q16.1 (IN), U13.2 (1Y)
/Outputs/IGN1_SRC: D31.2 (A), R15.2
/Outputs/IGN2_DRV: R16.1, U6.5 (OUT_B)
/Outputs/IGN2_SNK: Q17.1 (IN), U13.4 (2Y)
/Outputs/IGN2_SRC: D32.2 (A), R16.2
/Outputs/IGN3_DRV: R17.1, U7.7 (OUT_A)
/Outputs/IGN3_SNK: Q18.1 (IN), U13.6 (3Y)
/Outputs/IGN3_SRC: D33.2 (A), R17.2
/Outputs/IGN4_DRV: R18.1, U7.5 (OUT_B)
/Outputs/IGN4_SNK: Q19.1 (IN), U13.8 (4Y)
/Outputs/IGN4_SRC: D34.2 (A), R18.2
/Outputs/INJ1_CL: D42.1 (K), D46.1 (K)
/Outputs/INJ1_DRV: R152.1, U11.10 (A8)
/Outputs/INJ1_IN: Q1.1 (IN), R19.1, R152.2
/Outputs/INJ2_CL: D43.1 (K), D47.1 (K)
/Outputs/INJ2_DRV: R153.1, U11.9 (A7)
/Outputs/INJ2_IN: Q2.1 (IN), R20.1, R153.2
/Outputs/INJ3_CL: D44.1 (K), D48.1 (K)
/Outputs/INJ3_DRV: R154.1, U11.8 (A6)
/Outputs/INJ3_IN: Q3.1 (IN), R21.1, R154.2
/Outputs/INJ4_CL: D45.1 (K), D49.1 (K)
/Outputs/INJ4_DRV: R155.1, U11.7 (A5)
/Outputs/INJ4_IN: Q4.1 (IN), R22.1, R155.2
/Outputs/LS7_G: Q15.1 (IN), RN3.3 (R3.1), U12.4 (A2)
/Outputs/MAINRLY_G: Q10.1 (IN), RN2.2 (R2.1), U12.9 (A7)
/Outputs/TACH_G: Q14.1 (IN), RN3.2 (R2.1), U12.5 (A3)
/Outputs/VVT_DRV: R157.1, U11.5 (A3)
/Outputs/VVT_IN: Q6.1 (IN), R24.1, R157.2
AC_CTL: U12.16 (B6); also elsewhere on the board
ALT_CTL: U11.21 (B1); also elsewhere on the board
BOOST_CTL: U11.20 (B2); also elsewhere on the board
CEL_CTL: R160.1; also elsewhere on the board
DRV_EN_N: R71.2, U11.22 (~OE), U12.22 (~OE); also elsewhere on the board
FAN_CTL: U12.17 (B5); also elsewhere on the board
FP_CTL: U12.14 (B8); also elsewhere on the board
GND: C34.2, C35.2, C57.2, C58.2, C64.2, C65.2, C66.2, Q1.3 (S), Q2.3 (S), Q3.3 (S), Q4.3 (S), Q5.3 (S), Q6.3 (S), Q7.3 (S), Q8.3 (S), Q9.2 (S), Q10.2 (S), Q11.2 (S), Q12.2 (S), Q13.2 (S), Q14.2 (S), Q15.2 (S), Q16.2 (S), Q17.2 (S), Q18.2 (S), Q19.2 (S), R19.2, R20.2, R21.2, R22.2, R23.2, R24.2, R25.2, R26.2, R144.2, R145.2, R146.2, R147.2, RN1.5 (R4.2), RN1.6 (R3.2), RN1.7 (R2.2), RN1.8 (R1.2), RN2.5 (R4.2), RN2.6 (R3.2), RN2.7 (R2.2), RN2.8 (R1.2), RN3.4 (R4.1), RN3.5 (R4.2), RN3.6 (R3.2), RN3.7 (R2.2), RN3.8 (R1.2), U6.3 (GND), U7.3 (GND), U11.2 (DIR), U11.11 (GND), U11.12 (GND), U11.13 (GND), U12.2 (DIR), U12.11 (GND), U12.12 (GND), U12.13 (GND), U12.18 (B4), U12.21 (B1), U13.7 (GND), U13.11 (5A), U13.13 (6A); also elsewhere on the board
IACV_CTL: U11.18 (B4); also elsewhere on the board
IGN1_CTL: RN1.1 (R1.1), U6.2 (IN_A), U13.1 (1A); also elsewhere on the board
IGN2_CTL: RN1.2 (R2.1), U6.4 (IN_B), U13.3 (2A); also elsewhere on the board
IGN3_CTL: RN1.3 (R3.1), U7.2 (IN_A), U13.5 (3A); also elsewhere on the board
IGN4_CTL: RN1.4 (R4.1), U7.4 (IN_B), U13.9 (4A); also elsewhere on the board
INJ1_CTL: U11.14 (B8); also elsewhere on the board
INJ2_CTL: U11.15 (B7); also elsewhere on the board
INJ3_CTL: U11.16 (B6); also elsewhere on the board
INJ4_CTL: U11.17 (B5); also elsewhere on the board
LS7_CTL: U12.20 (B2); also elsewhere on the board
MAINRLY_CTL: U12.15 (B7); also elsewhere on the board
OUT_AC: Q11.3 (D); also elsewhere on the board
OUT_ALT: Q8.2 (D); also elsewhere on the board
OUT_BOOST: Q7.2 (D); also elsewhere on the board
OUT_CEL: Q13.3 (D); also elsewhere on the board
OUT_FAN: Q12.3 (D); also elsewhere on the board
OUT_FP: Q9.3 (D); also elsewhere on the board
OUT_IACV: Q5.2 (D); also elsewhere on the board
OUT_IGN1: D31.1 (K), Q16.3 (D), R144.1; also elsewhere on the board
OUT_IGN2: D32.1 (K), Q17.3 (D), R145.1; also elsewhere on the board
OUT_IGN3: D33.1 (K), Q18.3 (D), R146.1; also elsewhere on the board
OUT_IGN4: D34.1 (K), Q19.3 (D), R147.1; also elsewhere on the board
OUT_INJ1: D42.2 (A), Q1.2 (D); also elsewhere on the board
OUT_INJ2: D43.2 (A), Q2.2 (D); also elsewhere on the board
OUT_INJ3: D44.2 (A), Q3.2 (D); also elsewhere on the board
OUT_INJ4: D45.2 (A), Q4.2 (D); also elsewhere on the board
OUT_LS7: Q15.3 (D); also elsewhere on the board
OUT_MAINRLY: Q10.3 (D); also elsewhere on the board
OUT_TACH: Q14.3 (D); also elsewhere on the board
OUT_VVT: Q6.2 (D); also elsewhere on the board
TACH_CTL: U12.19 (B3); also elsewhere on the board
VBAT_IN: D46.2 (A), D47.2 (A), D48.2 (A), D49.2 (A); also elsewhere on the board
VVT_CTL: U11.19 (B3); also elsewhere on the board

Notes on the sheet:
Protected low-side drivers (VND7NV04, DPAK): injectors, IACV, VVT, boost, alternator
Ignition logic outputs: TC4427 sources through 100 R + Schottky; ZXMS6004 pulls low (gate = inverted control)
Ignition inputs pulled low (coils stay off while the MCU boots)
Relay, lamp and tach outputs: ZXMS6004 protected low sides, 5 V gates from U12 (enabled with the drivers)
rev 0.10: CEL gate straight from the MCU (lights on a fatal error)
3.3 V -> 5 V level shifter for the low-side inputs (DIR low: B -> A)
~OE pulled up: all eight drivers off until the firmware drives DRV_EN_N low
